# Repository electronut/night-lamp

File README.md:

### Project

A 555 based motion sensing night lamp kit for kids. You can read about the project here:

http://electronut.in/night-lamp/

### Schematic

Here is the schematic:

### PCB

You can order the PCB from the OSH Park link below:

https://oshpark.com/shared_projects/wEVw0g1x

### License

<br /><span xmlns:dct="http://purl.org/dc/terms/" property="dct:title">Motion Sensing Night Lamp Kit</span> by <a xmlns:cc="http://creativecommons.org/ns#" href="electronut.in" property="cc:attributionName" rel="cc:attributionURL">Mahesh Venkitachalam</a> is licensed under a <a rel="license" href="http://creativecommons.org/licenses/by-sa/4.0/">Creative Commons Attribution-ShareAlike 4.0 International License</a>.

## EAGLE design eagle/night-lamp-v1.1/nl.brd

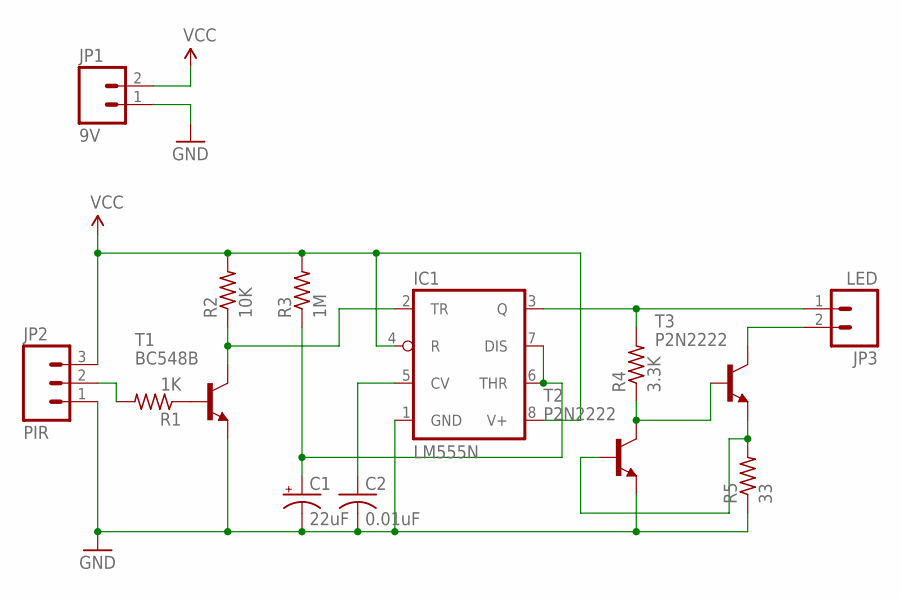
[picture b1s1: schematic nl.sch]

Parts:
C1: 22uF; E5-6
C2: 0.01uF; C025-024X044
IC1: LM555N; DIL08-ROUND
JP1: 9V; 1X02
JP2: PIR; 1X03
JP3: LED; 1X02
R1: 1K; 0309/12
R2: 10K; 0309/12
R3: 1M; 0309/12
R4: 3.3K; 0309/12
R5: 33; 0309/12
T1: BC548B; TO92-EBC
T2, T3: P2N2222; TO92-EBC

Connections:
GND: C1.-, C2.2, IC1.1 (GND), JP1.1, JP2.1, R5.1, T1.E, T2.E
unnamed: R1.1, T1.B
unnamed: JP2.2, R1.2
unnamed: R5.2, T2.B, T3.E
unnamed: C2.1, IC1.5 (CV)
unnamed: JP3.2, T3.C
unnamed: IC1.3 (Q), JP3.1, R4.2
unnamed: IC1.2 (TR), R2.1, T1.C
unnamed: C1.+, IC1.6 (THR), IC1.7 (DIS), R3.1
unnamed: R4.1, T2.C, T3.B
VCC: IC1.4 (R), IC1.8 (V+), JP1.2, JP2.3, R2.2, R3.2

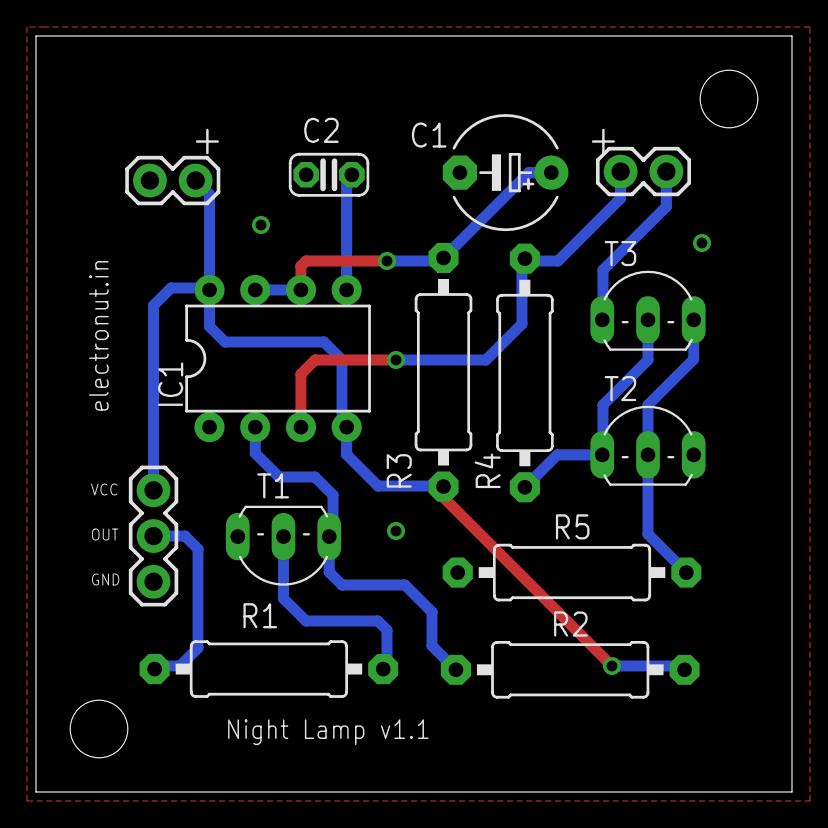
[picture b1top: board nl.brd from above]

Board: 2 copper layers, 42.0 x 42.0 mm, 14 parts (0 on the bottom side), 11 nets.

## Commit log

2015-06-18 initial

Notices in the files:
parts and their libraries:
SparkFun-Connectors: Licensing: CC v3.0 Share-Alike You are welcome to use this library for commercial purposes.
